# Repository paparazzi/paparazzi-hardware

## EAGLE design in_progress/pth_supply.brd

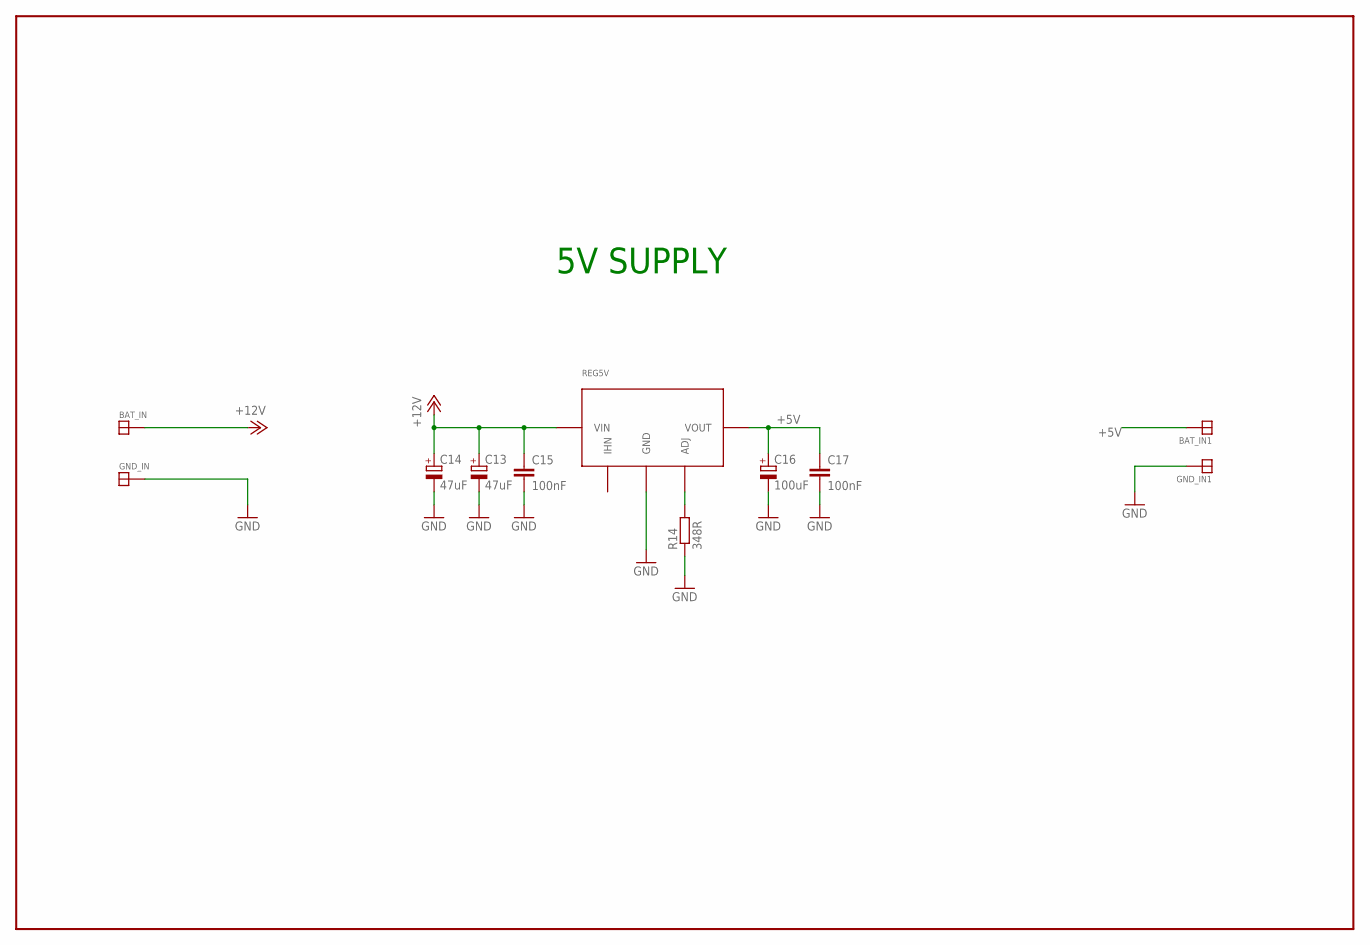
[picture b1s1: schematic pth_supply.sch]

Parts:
BAT_IN, BAT_IN1: SOLDER_PAD150_75; SOLD_PAD_150_75
C13, C14: 47uF; SMC_D
C15, C17: 100nF; C0805K
C16: 100uF; SMC_D
GND_IN, GND_IN1: SOLDER_PAD150_75; SOLD_PAD_150_75
R14: 348R; R1206
REG5V: PTH

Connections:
+5V: BAT_IN1.P$1, C16.+, C17.1, REG5V.P$3 (VOUT)
+12V: BAT_IN.P$1, C13.+, C14.+, C15.1, REG5V.P$1 (VIN)
GND: C13.-, C14.-, C15.2, C16.-, C17.2, GND_IN.P$1, GND_IN1.P$1, R14.1, REG5V.P$2 (GND)
unnamed: R14.2, REG5V.P$4 (ADJ)

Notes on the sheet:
5V SUPPLY

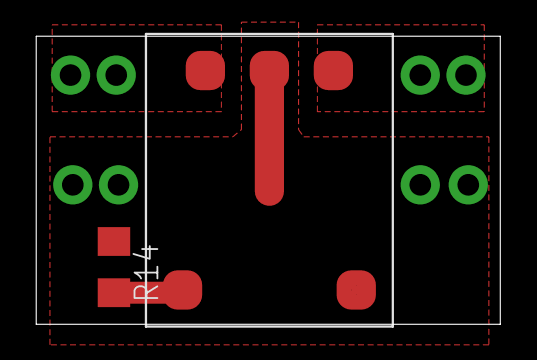
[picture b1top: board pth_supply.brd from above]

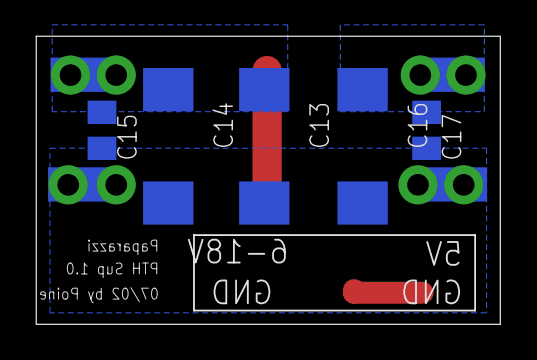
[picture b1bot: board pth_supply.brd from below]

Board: 2 copper layers, 25.8 x 16.0 mm, 11 parts (9 on the bottom side), 4 nets.

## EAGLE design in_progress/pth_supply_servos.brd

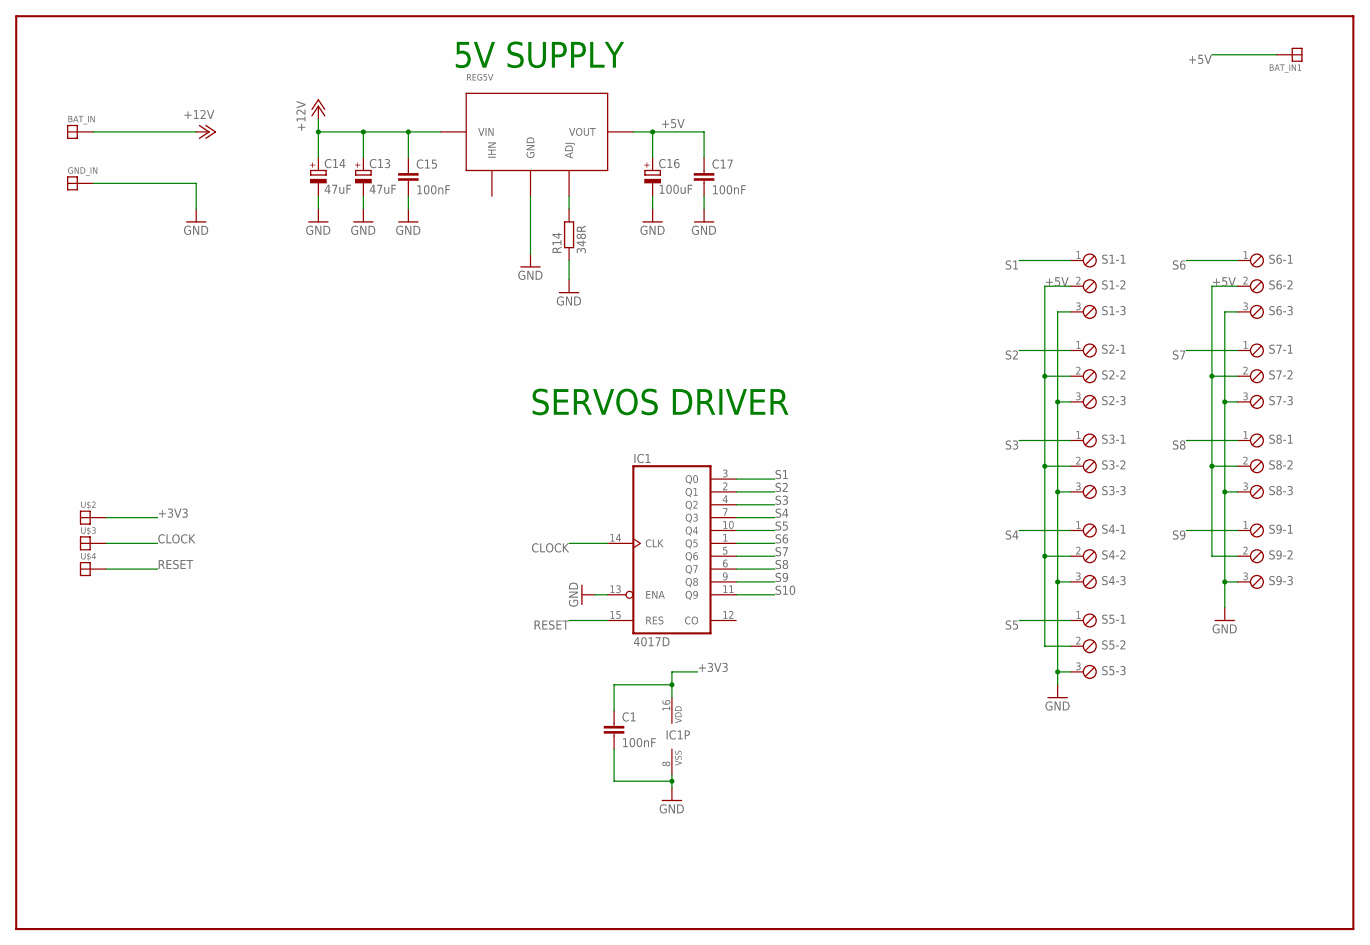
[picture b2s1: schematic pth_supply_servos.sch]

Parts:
BAT_IN, BAT_IN1: SOLDER_PAD150_75; SOLD_PAD_150_75
C1, C15, C17: 100nF; C0805K
C13, C14: 47uF; SMC_D
C16: 100uF; SMC_D
GND_IN: SOLDER_PAD150_75; SOLD_PAD_150_75
IC1: 4017D; SO16
R14: 348R; R0805
REG5V: PTH
S1, S2, S3, S4, S5, S6, S7, S8, S9: MPT3; 3POL254
U$2, U$3, U$4: SOLDER_PAD100_50; SOLDER_PAD_100_50

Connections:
+3V3: C1.1, IC1.16 (VDD), U$2.P$1
+5V: BAT_IN1.P$1, C16.+, C17.1, REG5V.P$3 (VOUT), S1.2, S2.2, S3.2, S4.2, S5.2, S6.2, S7.2, S8.2, S9.2
+12V: BAT_IN.P$1, C13.+, C14.+, C15.1, REG5V.P$1 (VIN)
CLOCK: IC1.14 (CLK), U$3.P$1
GND: C1.2, C13.-, C14.-, C15.2, C16.-, C17.2, GND_IN.P$1, IC1.8 (VSS), IC1.13 (ENA), R14.1, REG5V.P$2 (GND), S1.3, S2.3, S3.3, S4.3, S5.3, S6.3, S7.3, S8.3, S9.3
unnamed: R14.2, REG5V.P$4 (ADJ)
RESET: IC1.15 (RES), U$4.P$1
S1: IC1.3 (Q0), S1.1
S2: IC1.2 (Q1), S2.1
S3: IC1.4 (Q2), S3.1
S4: IC1.7 (Q3), S4.1
S5: IC1.10 (Q4), S5.1
S6: IC1.1 (Q5), S6.1
S7: IC1.5 (Q6), S7.1
S8: IC1.6 (Q7), S8.1
S9: IC1.9 (Q8), S9.1
S10: IC1.11 (Q9)

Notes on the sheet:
5V SUPPLY
SERVOS DRIVER

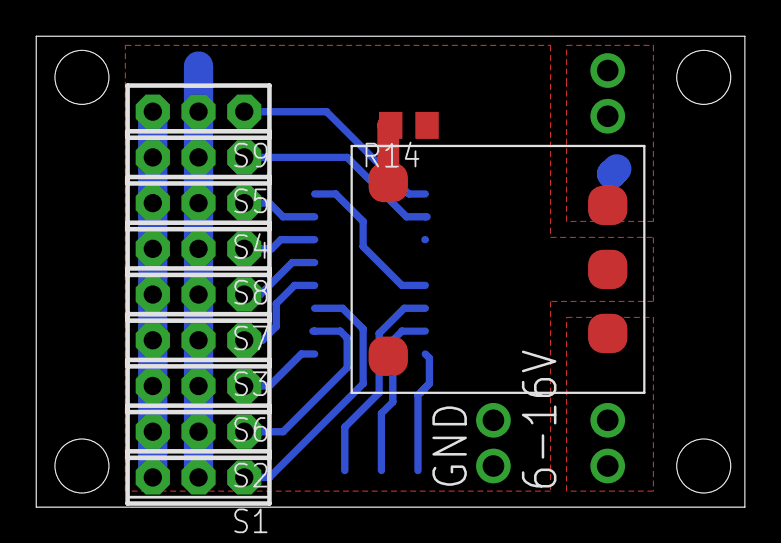
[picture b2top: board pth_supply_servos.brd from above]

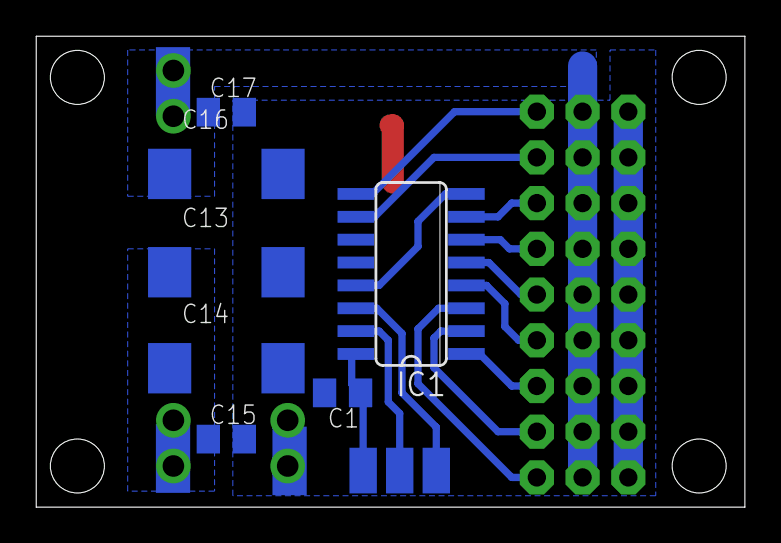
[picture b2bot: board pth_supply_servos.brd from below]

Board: 2 copper layers, 39.4 x 26.2 mm, 24 parts (13 on the bottom side), 16 nets.

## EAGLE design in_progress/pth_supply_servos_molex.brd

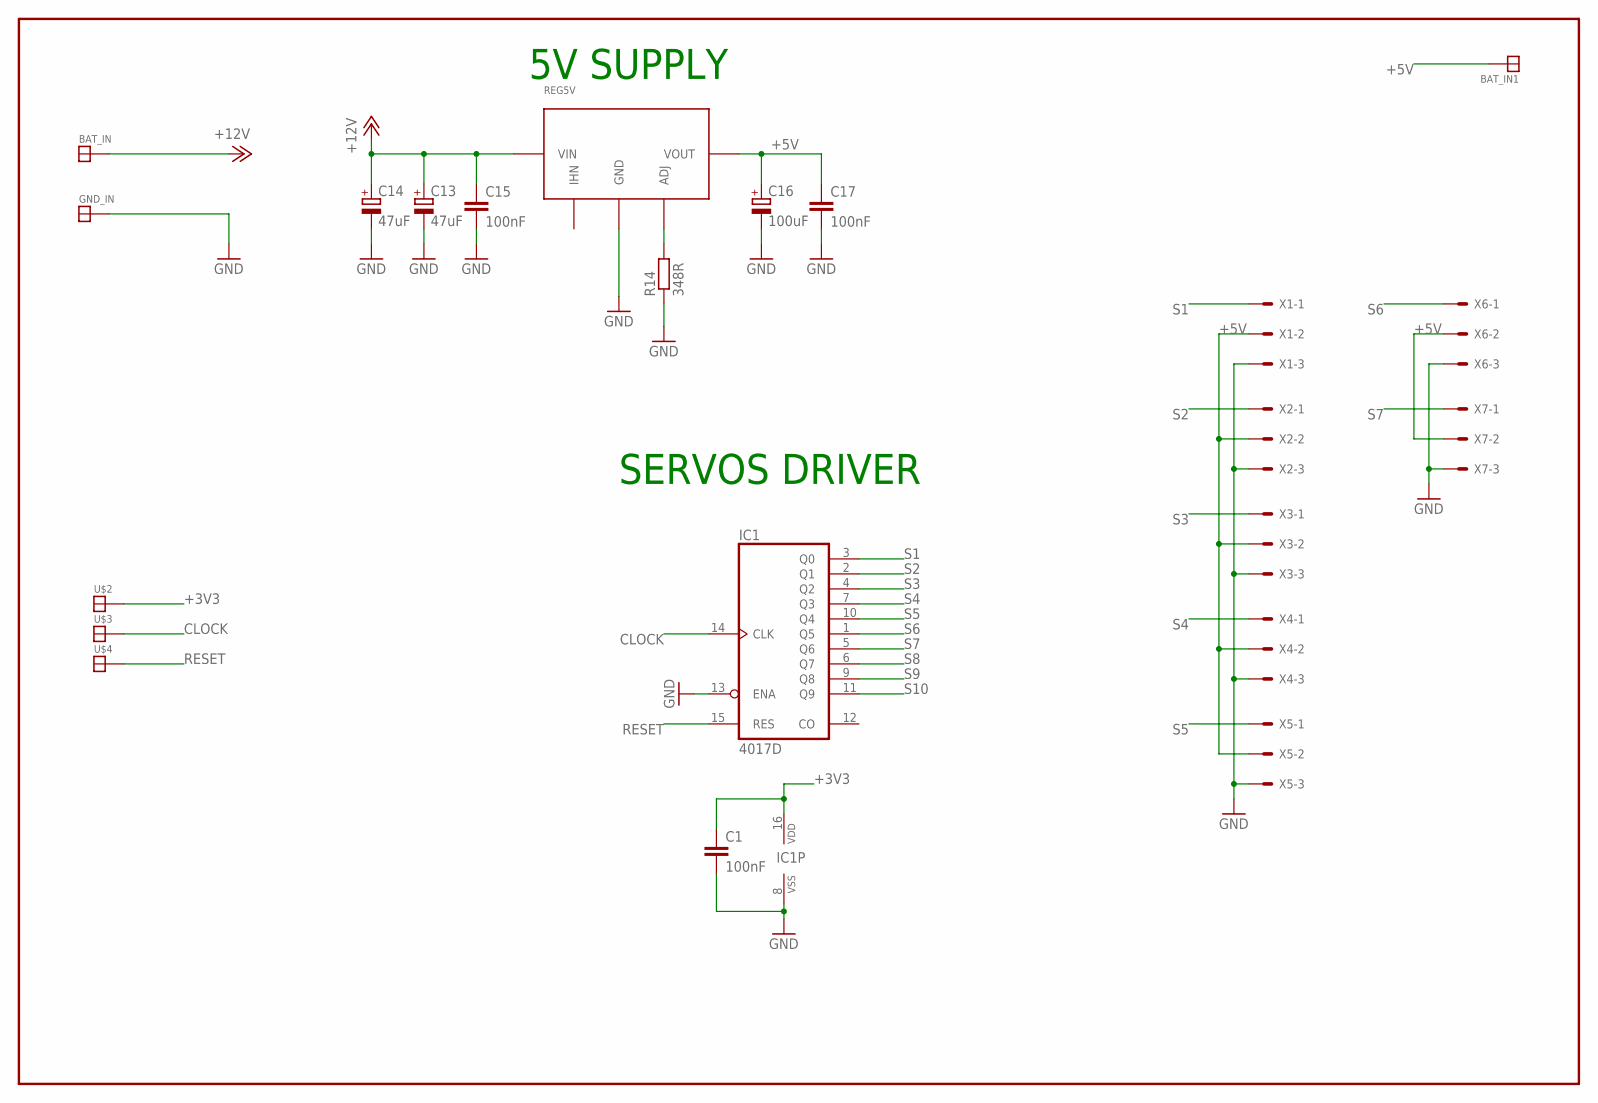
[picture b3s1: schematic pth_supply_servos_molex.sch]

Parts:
BAT_IN, BAT_IN1: SOLDER_PAD150_75; SOLD_PAD_150_75
C1, C15, C17: 100nF; C0805K
C13, C14: 47uF; SMC_D
C16: 100uF; SMC_D
GND_IN: SOLDER_PAD150_75; SOLD_PAD_150_75
IC1: 4017D; SO16
R14: 348R; R0805
REG5V: PTH
U$2, U$3, U$4: SOLDER_PAD100_50; SOLDER_PAD_100_50
X1, X2, X3, X4, X5, X6, X7: 53047-03

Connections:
+3V3: C1.1, IC1.16 (VDD), U$2.P$1
+5V: BAT_IN1.P$1, C16.+, C17.1, REG5V.P$3 (VOUT), X1.2, X2.2, X3.2, X4.2, X5.2, X6.2, X7.2
+12V: BAT_IN.P$1, C13.+, C14.+, C15.1, REG5V.P$1 (VIN)
CLOCK: IC1.14 (CLK), U$3.P$1
GND: C1.2, C13.-, C14.-, C15.2, C16.-, C17.2, GND_IN.P$1, IC1.8 (VSS), IC1.13 (ENA), R14.1, REG5V.P$2 (GND), X1.3, X2.3, X3.3, X4.3, X5.3, X6.3, X7.3
unnamed: R14.2, REG5V.P$4 (ADJ)
RESET: IC1.15 (RES), U$4.P$1
S1: IC1.3 (Q0), X1.1
S2: IC1.2 (Q1), X2.1
S3: IC1.4 (Q2), X3.1
S4: IC1.7 (Q3), X4.1
S5: IC1.10 (Q4), X5.1
S6: IC1.1 (Q5), X6.1
S7: IC1.5 (Q6), X7.1
S8: IC1.6 (Q7)
S9: IC1.9 (Q8)
S10: IC1.11 (Q9)

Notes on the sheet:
5V SUPPLY
SERVOS DRIVER

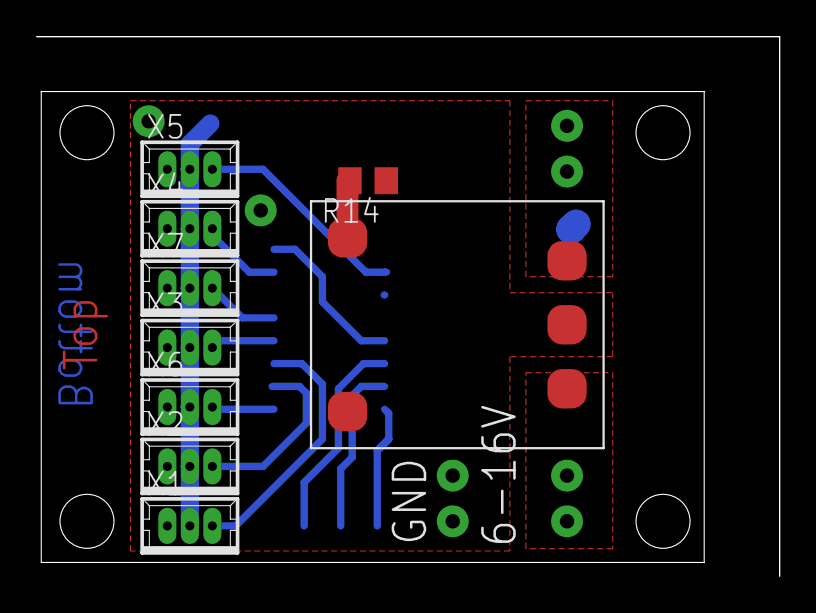
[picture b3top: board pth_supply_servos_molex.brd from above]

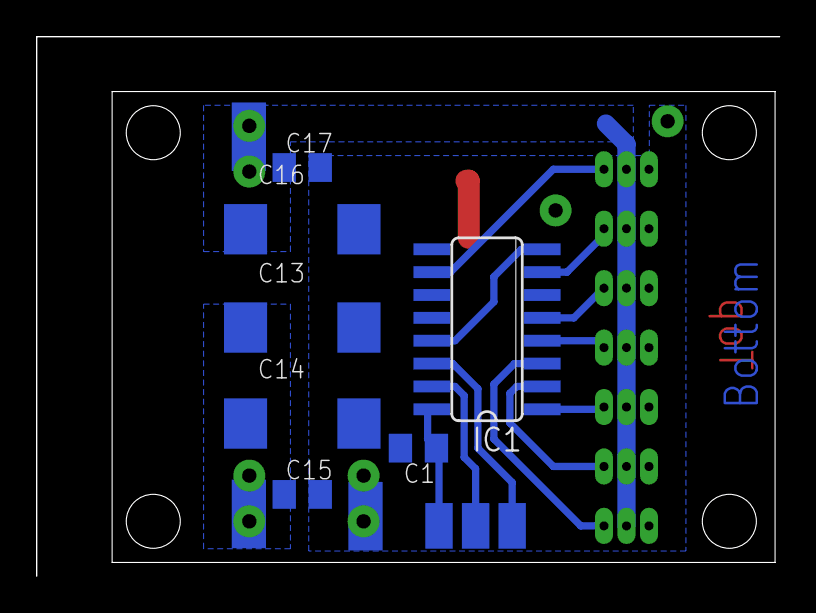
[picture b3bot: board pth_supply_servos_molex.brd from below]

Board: 2 copper layers, 36.8 x 26.2 mm, 22 parts (13 on the bottom side), 14 nets.

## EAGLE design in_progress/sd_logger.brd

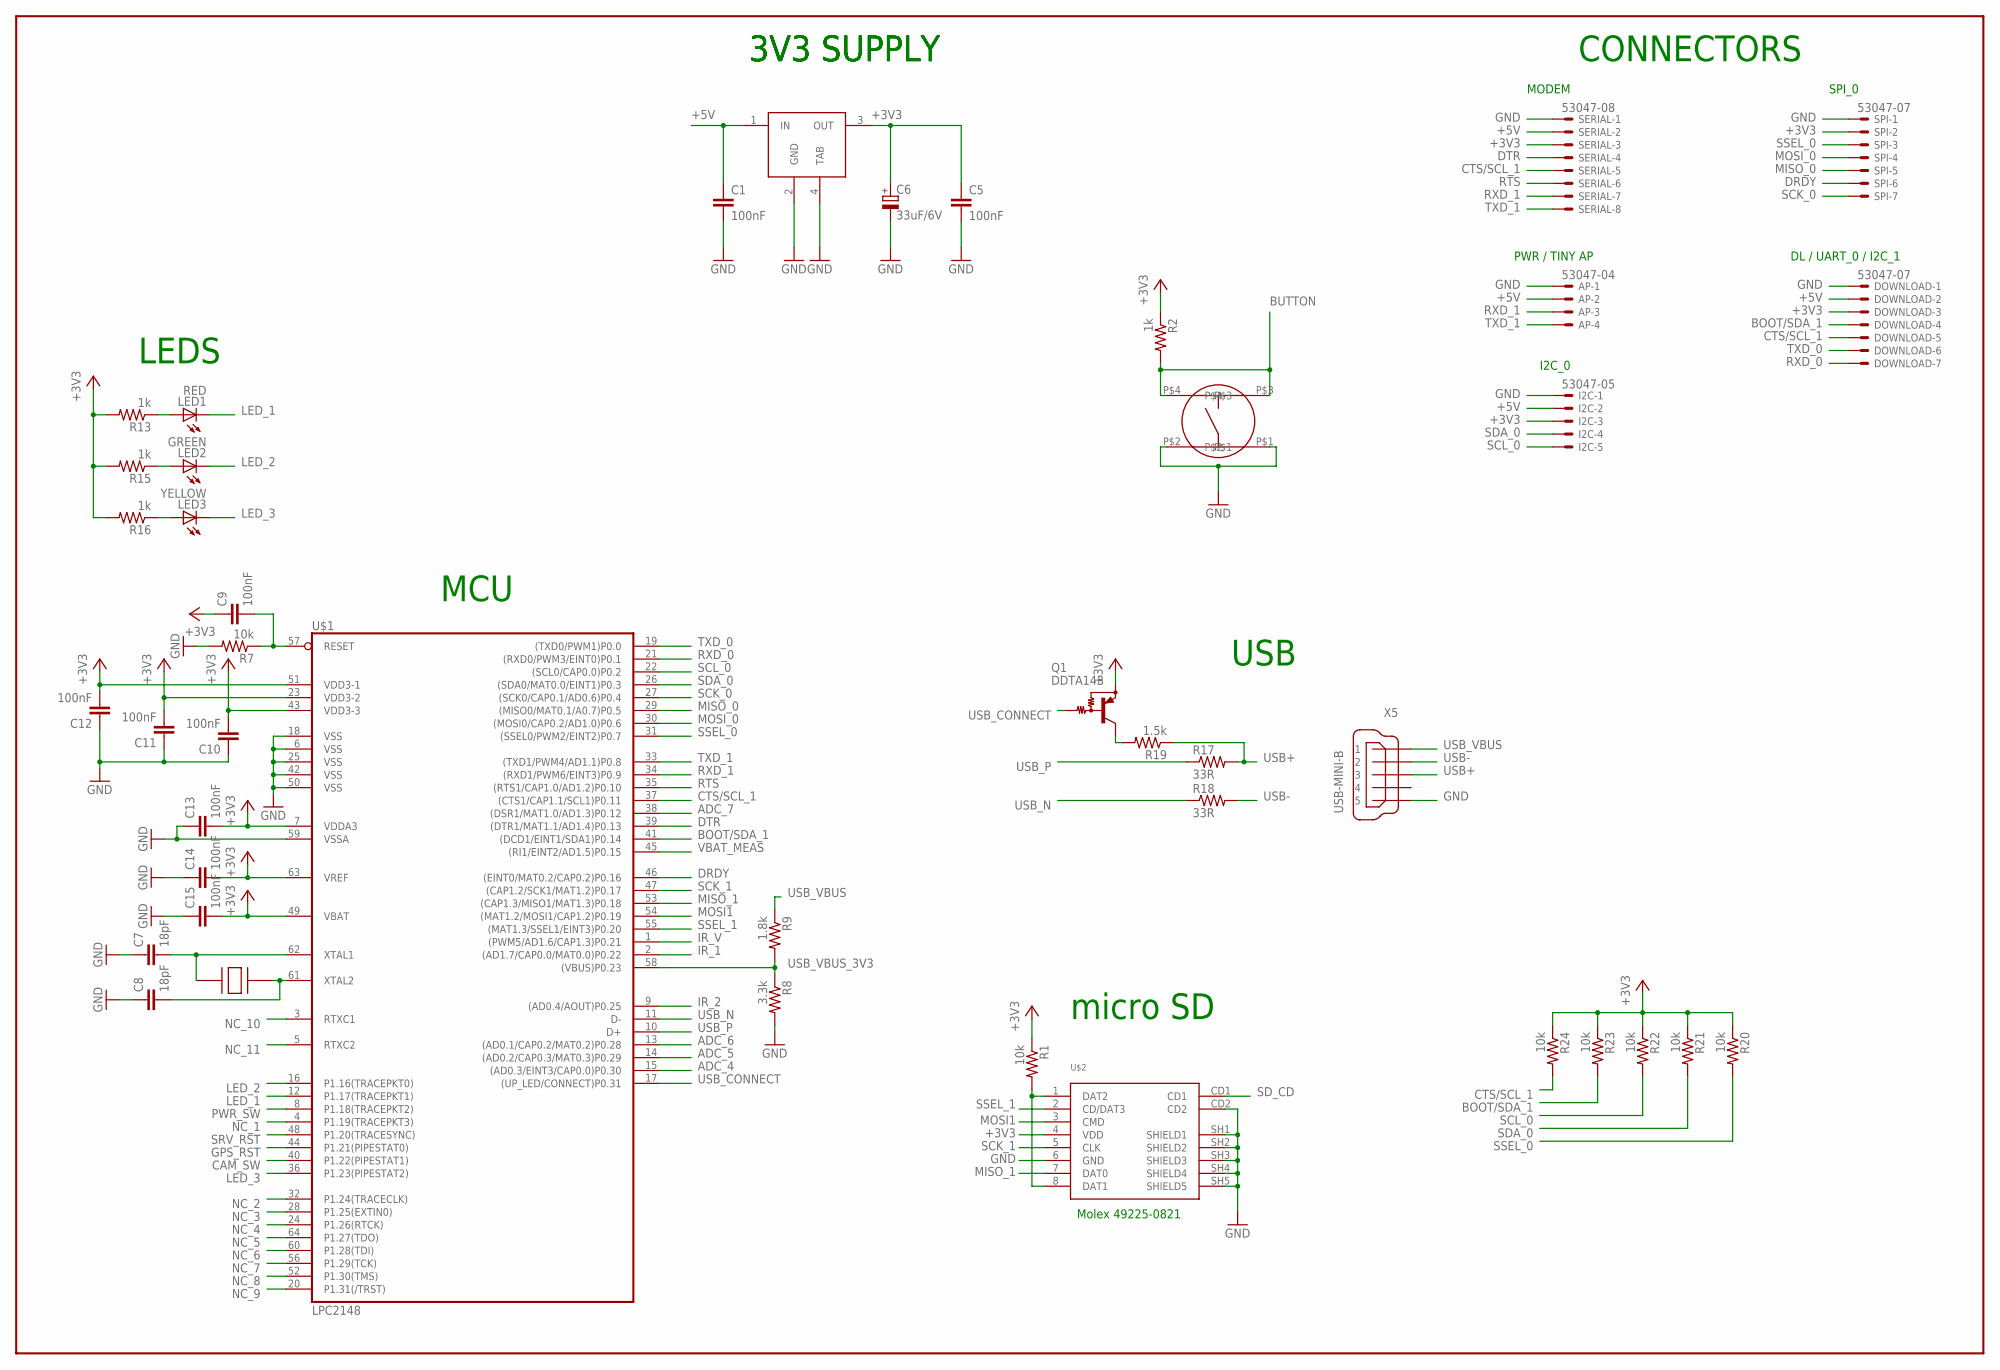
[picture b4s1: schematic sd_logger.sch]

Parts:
AP: 53047-04
C1, C5, C9, C10, C11, C12, C13, C14, C15: 100nF; C0603
C6: 33uF/6V; CT3216
C7, C8: 18pF; C0603
DOWNLOAD: 53047-07
I2C: 53047-05
LED1: RED; CHIP-LED0805
LED2: GREEN; CHIP-LED0805
LED3: YELLOW; CHIP-LED0805
Q1: DDTA143; SC59-BEC
R1, R7, R20, R21, R22, R23, R24: 10k; R0603@1
R2, R13, R15, R16: 1k; R0603@1
R8: 3.3k; R0603@1
R9: 1.8k; R0603@1
R17, R18: 33R; R0603@1
R19: 1.5k; R0603@1
SERIAL: 53047-08
SPI: 53047-07
SW1: B3S
U$1: LPC2148; SQFP-S-10X10-64
U$2: MICRO_SD; SD-MOLEX-49225
U$3: LM3940IMP-3.3; SOT223-R
U$4: CRYSTAL_CTS; CTS_CRYSTAL
X5: USB-MINI-B; UX60-MB-5ST

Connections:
+3V3: C5.1, C6.+, C9.1, C10.2, C11.2, C12.2, C13.2, C14.2, C15.2, DOWNLOAD.3, I2C.3, Q1.E, R1.1, R2.1, R13.2, R15.2, R16.2, R20.1, R21.1, R22.1, R23.1, R24.1, SERIAL.3, SPI.2, U$1.7 (VDDA3), U$1.23 (VDD3-2), U$1.43 (VDD3-3), U$1.49 (VBAT), U$1.51 (VDD3-1), U$1.63 (VREF), U$2.4 (VDD), U$3.3 (OUT)
+5V: AP.2, C1.1, DOWNLOAD.2, I2C.2, SERIAL.2, U$3.1 (IN)
ADC_4: U$1.15 ((AD0.3/EINT3/CAP0.0)P0.30)
ADC_5: U$1.14 ((AD0.2/CAP0.3/MAT0.3)P0.29)
ADC_6: U$1.13 ((AD0.1/CAP0.2/MAT0.2)P0.28)
ADC_7: U$1.38 ((DSR1/MAT1.0/AD1.3)P0.12)
BOOT/SDA_1: DOWNLOAD.4, R23.2, U$1.41 ((DCD1/EINT1/SDA1)P0.14)
BUTTON: R2.2, SW1.P$3, SW1.P$4
CAM_SW: U$1.40 (P1.22(PIPESTAT1))
CTS/SCL_1: DOWNLOAD.5, R24.2, SERIAL.5, U$1.37 ((CTS1/CAP1.1/SCL1)P0.11)
DRDY: SPI.6, U$1.46 ((EINT0/MAT0.2/CAP0.2)P0.16)
DTR: SERIAL.4, U$1.39 ((DTR1/MAT1.1/AD1.4)P0.13)
GND: AP.1, C1.2, C5.2, C6.-, C7.1, C8.1, C10.1, C11.1, C12.1, C13.1, C14.1, C15.1, DOWNLOAD.1, I2C.1, R7.2, R8.2, SERIAL.1, SPI.1, SW1.P$1, SW1.P$2, U$1.6 (VSS), U$1.18 (VSS), U$1.25 (VSS), U$1.42 (VSS), U$1.50 (VSS), U$1.59 (VSSA), U$2.6 (GND), U$2.CD2, U$2.SH1 (SHIELD1), U$2.SH2 (SHIELD2), U$2.SH3 (SHIELD3), U$2.SH4 (SHIELD4), U$2.SH5 (SHIELD5), U$3.2 (GND), U$3.4 (TAB), X5.5
GPS_RST: U$1.44 (P1.21(PIPESTAT0))
IR_1: U$1.2 ((AD1.7/CAP0.0/MAT0.0)P0.22)
IR_2: U$1.9 ((AD0.4/AOUT)P0.25)
IR_V: U$1.1 ((PWM5/AD1.6/CAP1.3)P0.21)
LED_1: LED1.C, U$1.12 (P1.17(TRACEPKT1))
LED_2: LED2.C, U$1.16 (P1.16(TRACEPKT0))
LED_3: LED3.C, U$1.36 (P1.23(PIPESTAT2))
LPC_RESET: C9.2, R7.1, U$1.57 (RESET)
MISO_0: SPI.5, U$1.29 ((MISO0/MAT0.1/A0.7)P0.5)
MISO_1: U$1.53 ((CAP1.3/MISO1/MAT1.3)P0.18), U$2.7 (DAT0)
MOSI1: U$1.54 ((MAT1.2/MOSI1/CAP1.2)P0.19), U$2.3 (CMD)
MOSI_0: SPI.4, U$1.30 ((MOSI0/CAP0.2/AD1.0)P0.6)
unnamed: LED1.A, R13.1
unnamed: C7.2, U$1.62 (XTAL1), U$4.P$1
unnamed: C8.2, U$1.61 (XTAL2), U$4.P$3
unnamed: LED2.A, R15.1
unnamed: LED3.A, R16.1
unnamed: R1.2, U$2.1 (DAT2), U$2.8 (DAT1)
unnamed: Q1.C, R19.2
NC_1: U$1.4 (P1.19(TRACEPKT3))
NC_2: U$1.32 (P1.24(TRACECLK))
NC_3: U$1.28 (P1.25(EXTIN0))
NC_4: U$1.24 (P1.26(RTCK))
NC_5: U$1.64 (P1.27(TDO))
NC_6: U$1.60 (P1.28(TDI))
NC_7: U$1.56 (P1.29(TCK))
NC_8: U$1.52 (P1.30(TMS))
NC_9: U$1.20 (P1.31(/TRST))
NC_10: U$1.3 (RTXC1)
NC_11: U$1.5 (RTXC2)
PWR_SW: U$1.8 (P1.18(TRACEPKT2))
RTS: SERIAL.6, U$1.35 ((RTS1/CAP1.0/AD1.2)P0.10)
RXD_0: DOWNLOAD.7, U$1.21 ((RXD0/PWM3/EINT0)P0.1)
RXD_1: AP.3, SERIAL.7, U$1.34 ((RXD1/PWM6/EINT3)P0.9)
SCK_0: SPI.7, U$1.27 ((SCK0/CAP0.1/AD0.6)P0.4)
SCK_1: U$1.47 ((CAP1.2/SCK1/MAT1.2)P0.17), U$2.5 (CLK)
SCL_0: I2C.5, R22.2, U$1.22 ((SCL0/CAP0.0)P0.2)
SDA_0: I2C.4, R21.2, U$1.26 ((SDA0/MAT0.0/EINT1)P0.3)
SD_CD: U$2.CD1
SRV_RST: U$1.48 (P1.20(TRACESYNC))
SSEL_0: R20.2, SPI.3, U$1.31 ((SSEL0/PWM2/EINT2)P0.7)
SSEL_1: U$1.55 ((MAT1.3/SSEL1/EINT3)P0.20), U$2.2 (CD/DAT3)
TXD_0: DOWNLOAD.6, U$1.19 ((TXD0/PWM1)P0.0)
TXD_1: AP.4, SERIAL.8, U$1.33 ((TXD1/PWM4/AD1.1)P0.8)
USB+: R17.2, R19.1, X5.3
USB-: R18.2, X5.2
USB_CONNECT: Q1.B, U$1.17 ((UP_LED/CONNECT)P0.31)
USB_N: R18.1, U$1.11 (D-)
USB_P: R17.1, U$1.10 (D+)
USB_VBUS: R9.1, X5.1
USB_VBUS_3V3: R8.1, R9.2, U$1.58 ((VBUS)P0.23)
VBAT_MEAS: U$1.45 ((RI1/EINT2/AD1.5)P0.15)

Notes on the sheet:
3V3 SUPPLY
MCU
LEDS
CONNECTORS
USB
micro SD
MODEM
PWR / TINY AP
I2C_0
SPI_0
DL / UART_0 / I2C_1
Molex 49225-0821

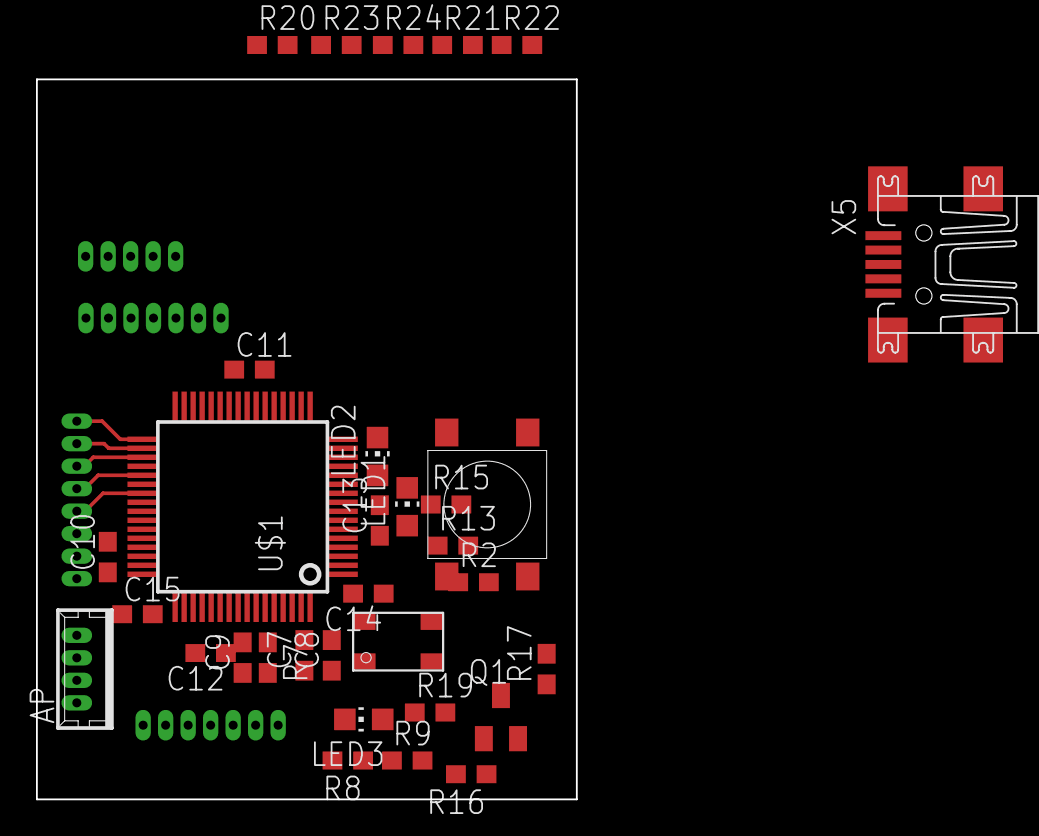
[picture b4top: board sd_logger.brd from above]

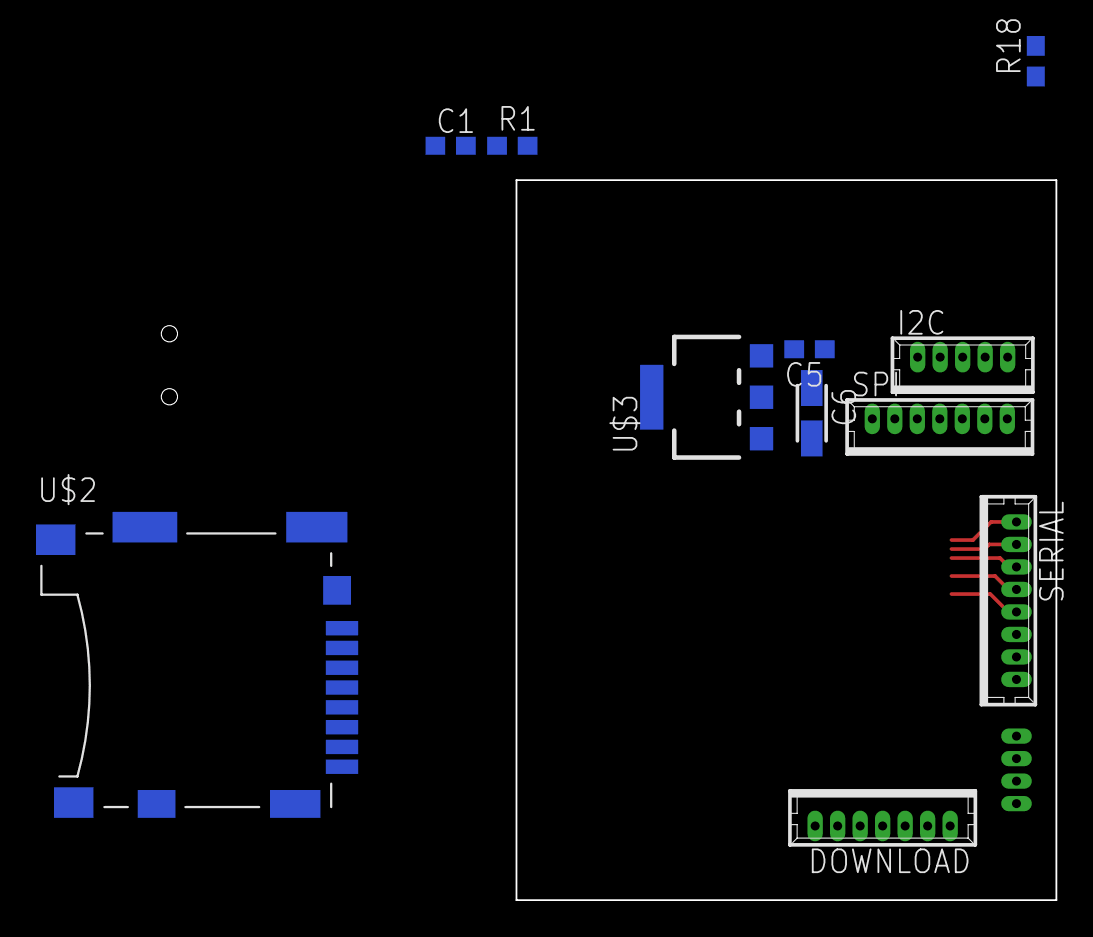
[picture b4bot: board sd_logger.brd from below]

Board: 4 copper layers, 30.0 x 40.0 mm, 43 parts (11 on the bottom side), 41 nets.

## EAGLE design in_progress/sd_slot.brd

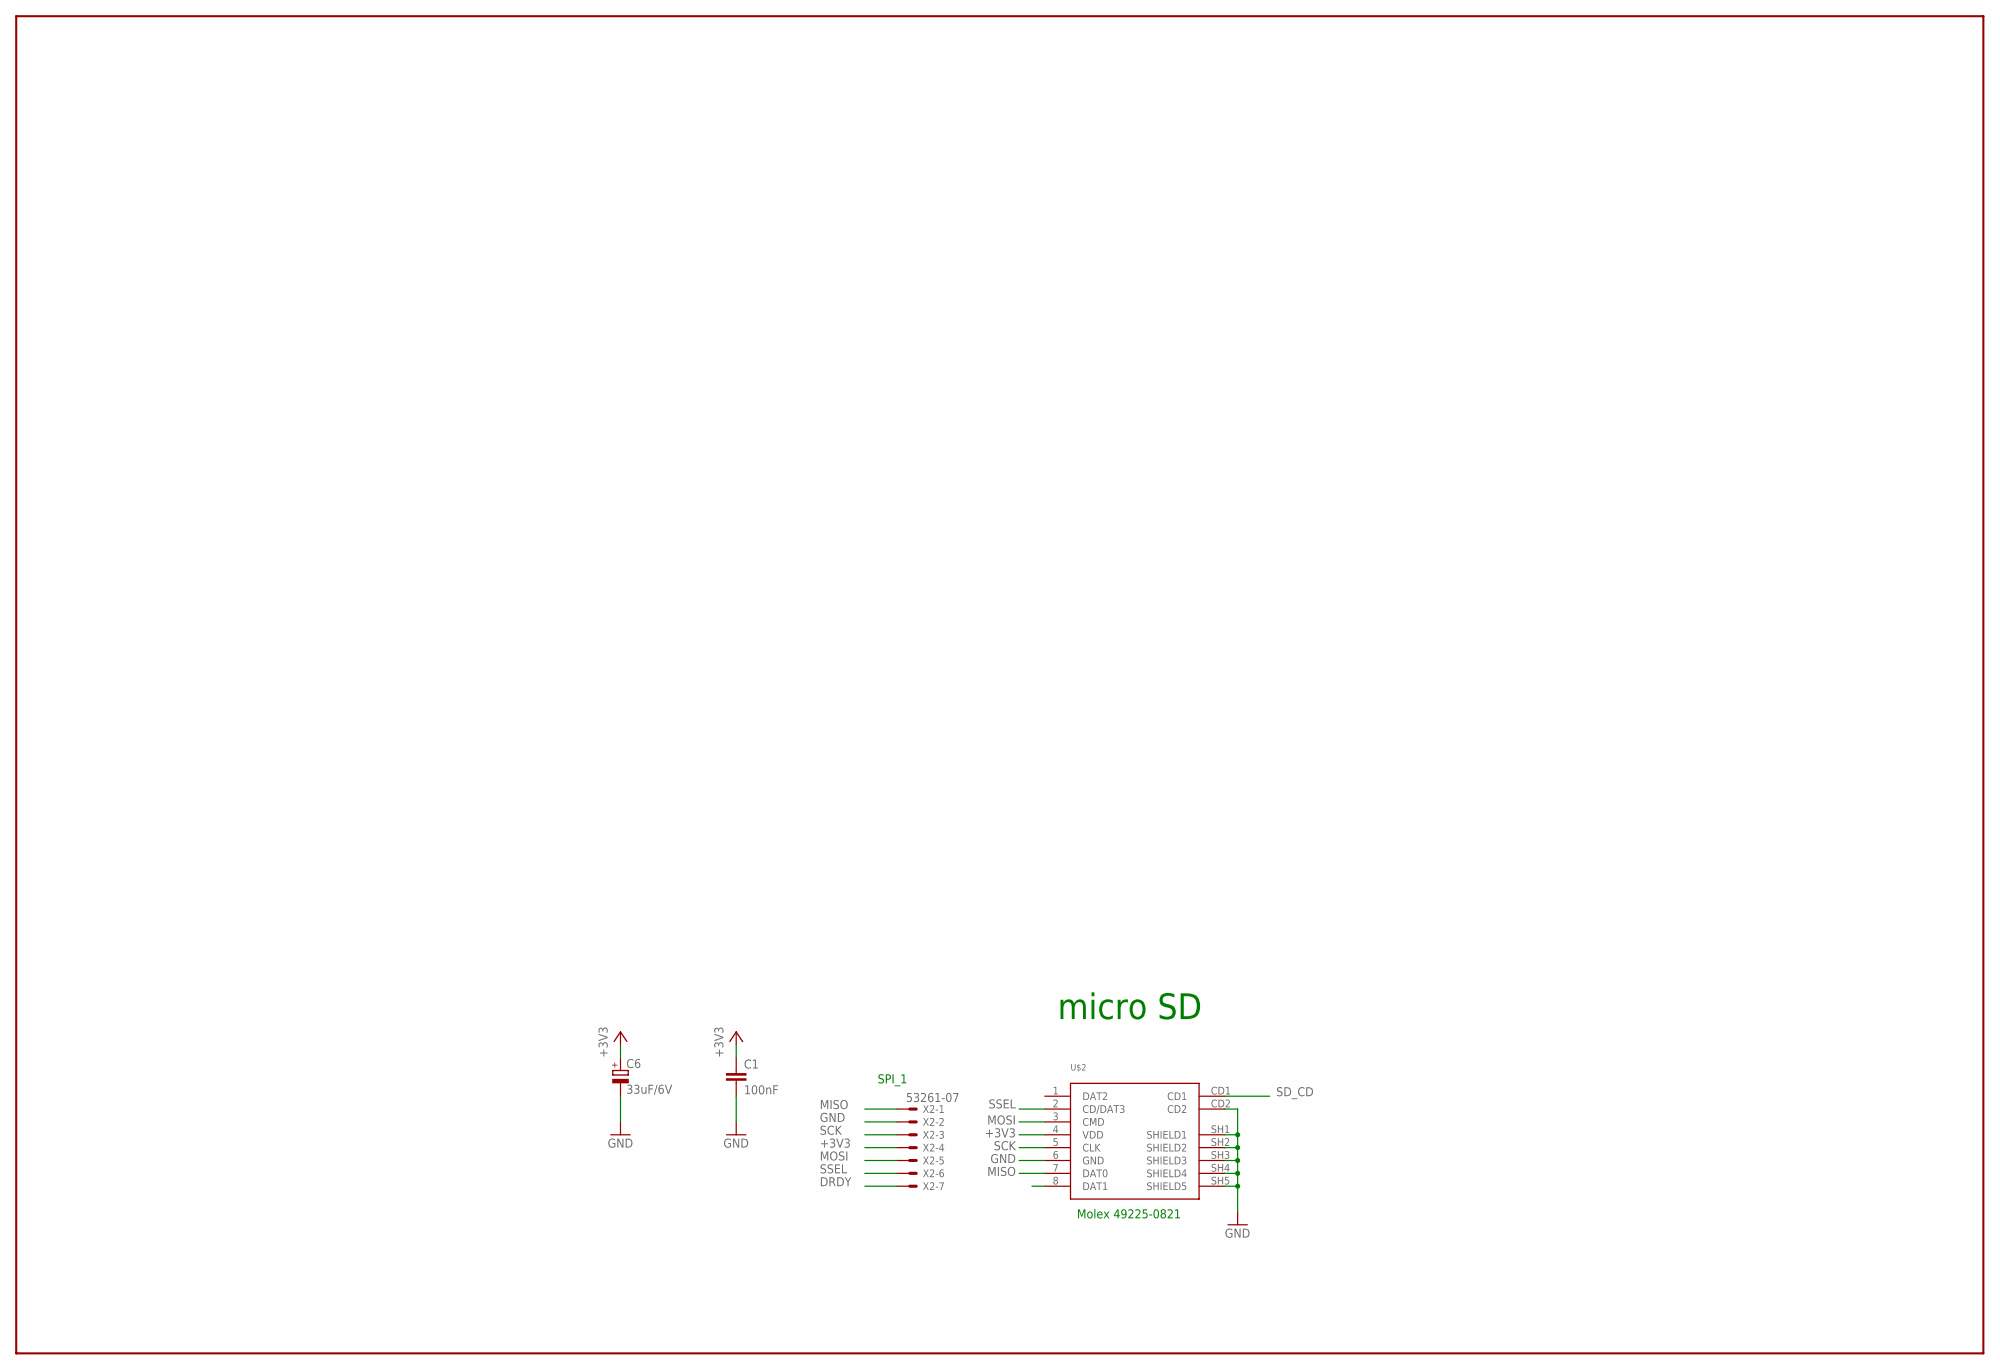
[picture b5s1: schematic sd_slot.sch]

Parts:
C1: 100nF; C0603
C6: 33uF/6V; CT3216
U$2: MICRO_SD; SD-MOLEX-49225
X2: 53261-07

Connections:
+3V3: C1.1, C6.+, U$2.4 (VDD), X2.4
DRDY: X2.7
GND: C1.2, C6.-, U$2.6 (GND), U$2.CD2, U$2.SH1 (SHIELD1), U$2.SH2 (SHIELD2), U$2.SH3 (SHIELD3), U$2.SH4 (SHIELD4), U$2.SH5 (SHIELD5), X2.2
MISO: U$2.7 (DAT0), X2.1
MOSI: U$2.3 (CMD), X2.5
SCK: U$2.5 (CLK), X2.3
SD_CD: U$2.CD1
SSEL: U$2.2 (CD/DAT3), X2.6

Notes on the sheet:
micro SD
Molex 49225-0821
SPI_1

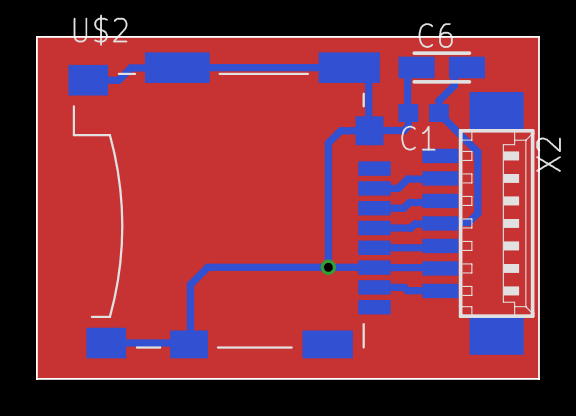
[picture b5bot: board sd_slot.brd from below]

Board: 4 copper layers, 27.9 x 19.0 mm, 4 parts (4 on the bottom side), 6 nets.

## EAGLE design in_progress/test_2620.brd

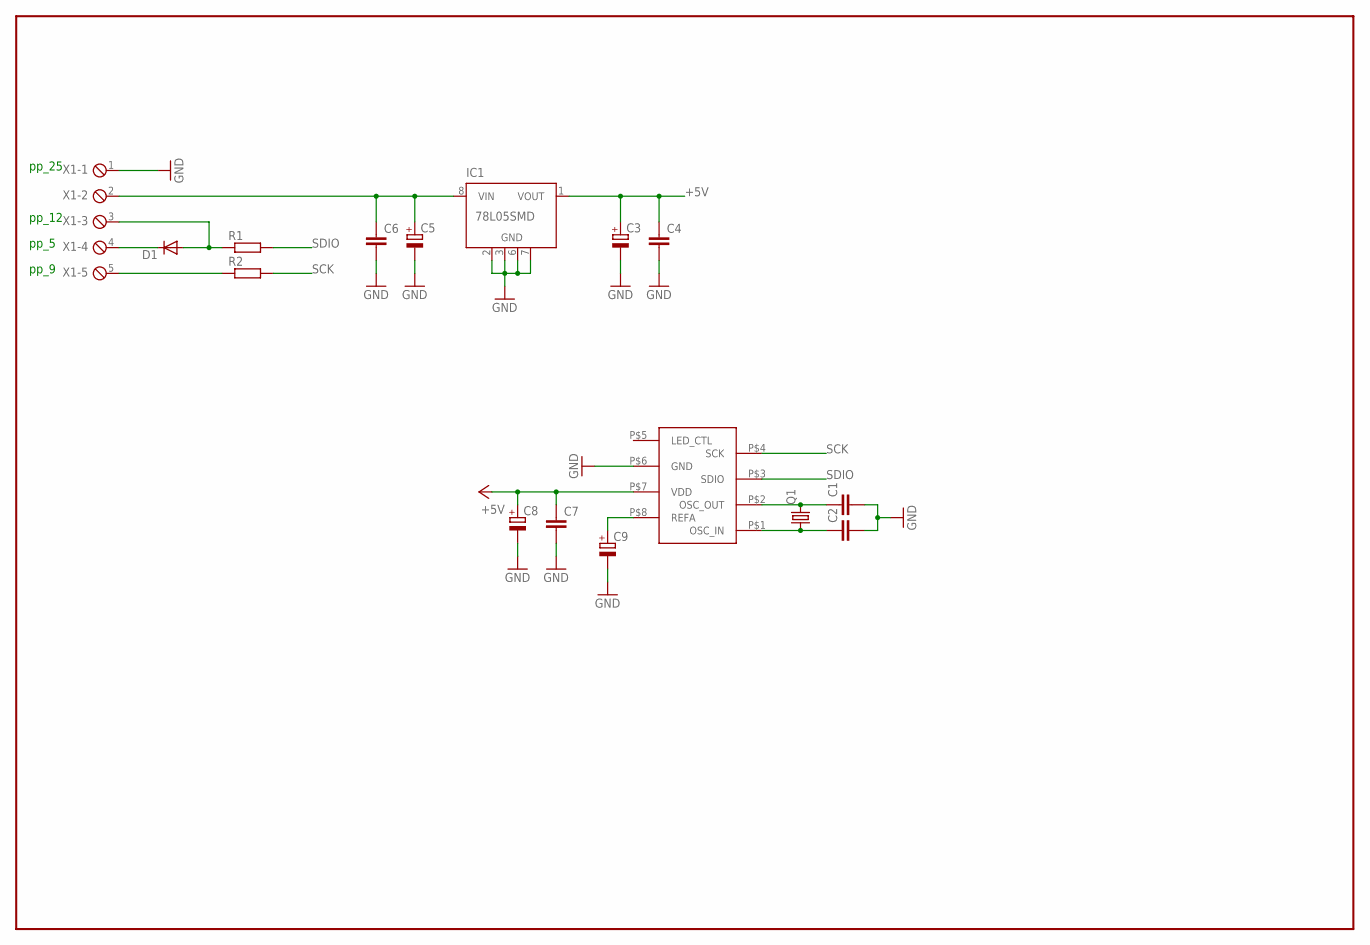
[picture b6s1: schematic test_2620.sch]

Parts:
C1, C2, C4, C6, C7: C-EUC0805K; C0805K
C3, C5, C8, C9: CPOL-EUSMCC; SMC_C
D1: DIODE-MINIMELF; MINIMELF
IC1: 78L05SMD; SO08
Q1: CRYTALHC49U-V; HC49U-V
R1, R2: R-EU_R0805; R0805
U$1: ADNS2620
X1: MPT5; 5POL254

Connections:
+5V: C3.+, C4.1, C7.1, C8.+, IC1.1 (VOUT), U$1.P$7 (VDD)
GND: C1.2, C2.2, C3.-, C4.2, C5.-, C6.2, C7.2, C8.-, C9.-, IC1.2 (GND), IC1.3 (GND), IC1.6 (GND), IC1.7 (GND), U$1.P$6 (GND), X1.1
unnamed: C1.1, Q1.2, U$1.P$2 (OSC_OUT)
unnamed: C2.1, Q1.1, U$1.P$1 (OSC_IN)
unnamed: C9.+, U$1.P$8 (REFA)
unnamed: D1.C, X1.4
unnamed: R2.1, X1.5
unnamed: D1.A, R1.1, X1.3
SCK: R2.2, U$1.P$4 (SCK)
SDIO: R1.2, U$1.P$3 (SDIO)
VBAT: C5.+, C6.1, IC1.8 (VIN), X1.2

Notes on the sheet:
pp_25
pp_12
pp_5
pp_9

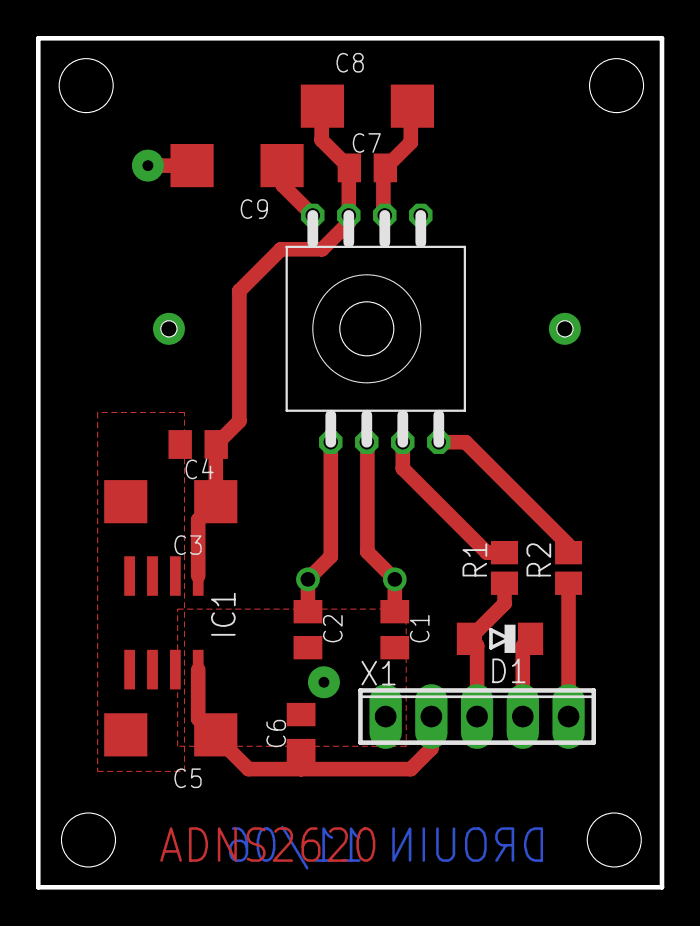
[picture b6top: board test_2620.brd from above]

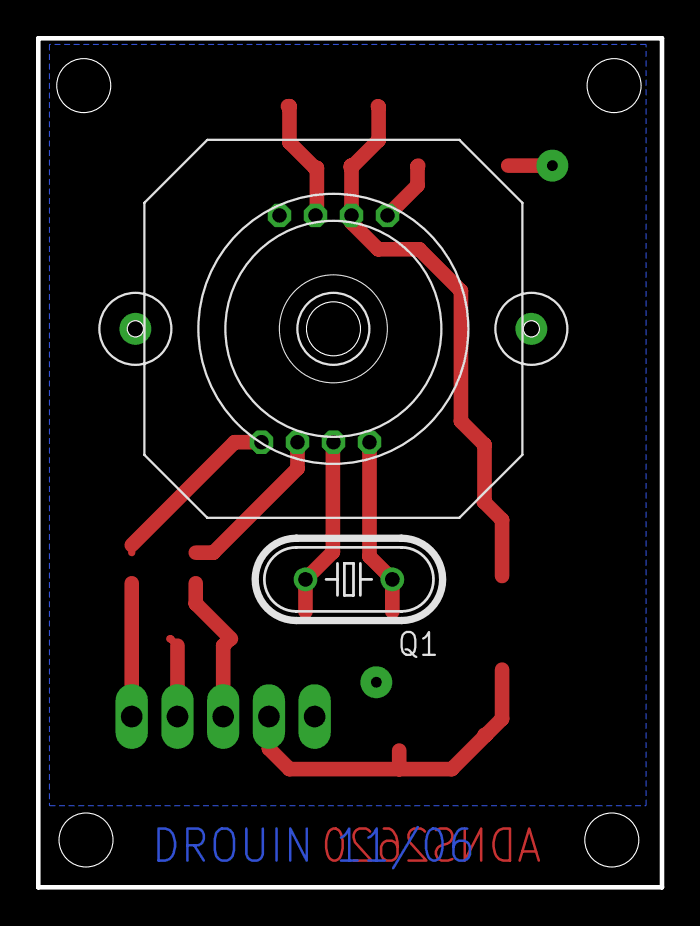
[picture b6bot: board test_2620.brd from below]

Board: 2 copper layers, 34.7 x 47.2 mm, 17 parts (2 on the bottom side), 11 nets.

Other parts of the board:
U$2: CAM_LENS
